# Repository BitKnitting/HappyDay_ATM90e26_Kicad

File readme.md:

## Version B

The B version of the HappyDay Energy PCB.  No changes to the schematic.  Several changes to the layout.  Corrected mistakes found while testing.

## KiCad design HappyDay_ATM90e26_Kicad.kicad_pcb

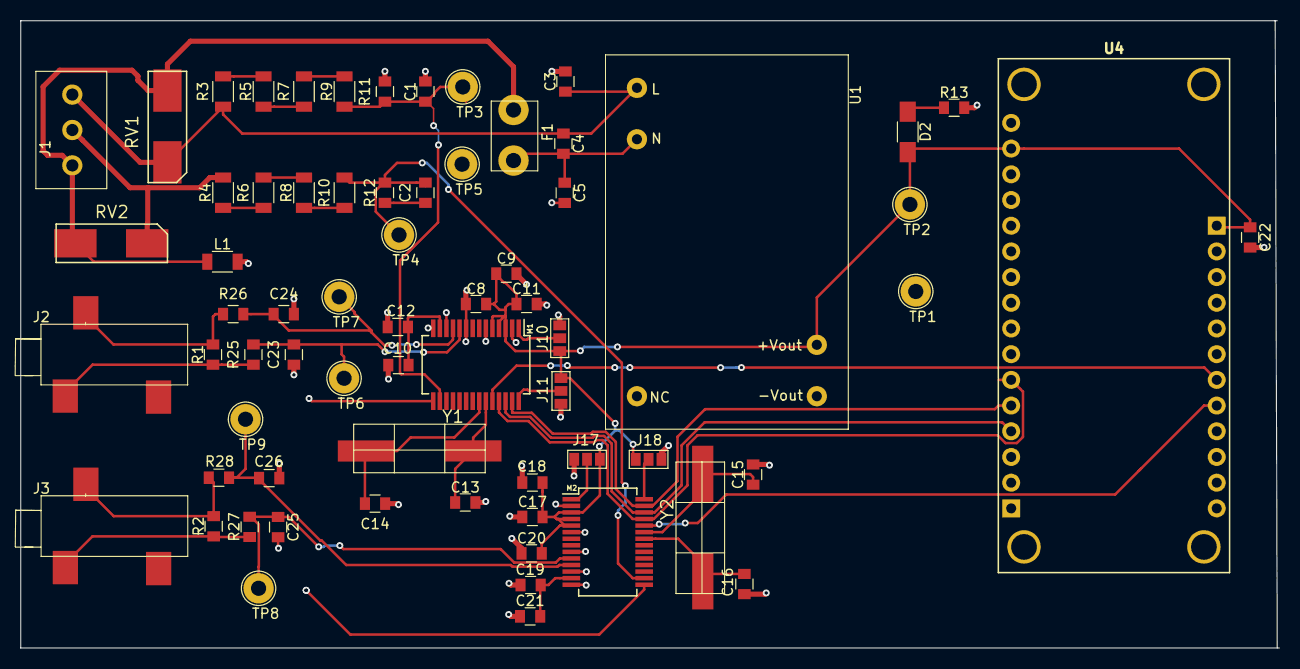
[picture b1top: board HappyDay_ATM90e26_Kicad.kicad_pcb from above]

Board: 2 copper layers, 124.4 x 62.0 mm, 68 parts (0 on the bottom side), 40 nets.

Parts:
C1, C2: .033u; C_0805
C3, C5: .001u; C_0805
C4, C8, C11, C12, C17, C20, C21, C22: .1u; C_0805
C9, C10, C18, C19: 10u; C_0805
C13, C14, C15, C16: 20p; C_0805
C23, C24, C25, C26: .33u; C_0805
D2: IND_LED; C_1206_HandSoldering
F1: Polyfuse; POLYFUSE
J1: Conn_01x03; 3PinConnector
J2, J3: TRS3.5; Audio-Jack
J10, J11, J17, J18: GS3
L1: Ferrite_Bead_Small; C_1206
M1, M2: ATM90E26_ATM90E26; SSOP-28_5.3x10.2mm_Pitch0.65mm
R1, R2: 12; C_0805
R3, R4, R5, R6, R7, R8, R9, R10: 220K; C_1206
R11, R12: 1K; C_0805
R13: 499; C_0805
R25, R26, R27, R28: 100; C_0805
RV1, RV2: Varistor; MOV
TP1: GNDD; Test_Point_Loop_D2.54mm_Drill1.5mm_Beaded
TP2: 3.3V; Test_Point_Loop_D2.54mm_Drill1.5mm_Beaded
TP3: LO_SAMP; Test_Point_Loop_D2.54mm_Drill1.5mm_Beaded
TP4: L1_SAMP; Test_Point_Loop_D2.54mm_Drill1.5mm_Beaded
TP5: GNDA; Test_Point_Loop_D2.54mm_Drill1.5mm_Beaded
TP6: IP_0; Test_Point_Loop_D2.54mm_Drill1.5mm_Beaded
TP7: IN_0; Test_Point_Loop_D2.54mm_Drill1.5mm_Beaded
TP8: IP_1; Test_Point_Loop_D2.54mm_Drill1.5mm_Beaded
TP9: IN_1; Test_Point_Loop_D2.54mm_Drill1.5mm_Beaded
U1: RAC03-3.3SGA; RAC03-GA
U4: FeatherHuzzah; ADAFRUIT_FEATHER
Y1, Y2: Crystal_Small; Crystal

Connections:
+3V3: C8.2, C9.1, C11.1, C17.2, C18.1, C20.1, C22.1, D2.2, J10.3, J11.1, J17.3, J18.1, M1.3, M1.4, M1.5, M2.3, M2.4, M2.5, TP2.1, U1.5, U4.15, U4.17
/ATM90_Circuit/CLKIN_0: C14.1, M1.22, Y1.2
/ATM90_Circuit/CLKIN_1: C16.1, M2.22, Y2.2
/ATM90_Circuit/CLKOUT_0: C13.1, M1.23, Y1.1
/ATM90_Circuit/CLKOUT_1: C15.1, M2.23, Y2.1
/ATM90_Circuit/CS0: M1.24, U4.23
/ATM90_Circuit/CS1: M2.24, U4.24
/ATM90_Circuit/MISO: M1.26, M2.26, U4.4
/ATM90_Circuit/MOSI: M1.27, M2.27, U4.5
/ATM90_Circuit/SCLK: M1.25, M2.25, U4.6
/IN_0: C24.2, M1.11, R26.1, TP7.1
/IN_1: C26.2, M2.11, R28.1, TP9.1
/IP_0: C23.1, M1.10, R25.1, TP6.1
/IP_1: C25.1, M2.10, R27.1, TP8.1
/L1: J1.2, R4.2, RV2.2
/L1_SAMP: C2.1, M2.16, R10.1, R12.2, TP4.1
/LO: C3.1, C4.1, J1.1, R3.2, RV1.2, U1.1
/LO_SAMP: C1.1, M1.16, R9.1, R11.2, TP3.1
/N: F1.2, J1.3, L1.1, RV1.1, RV2.1
GNDA: C1.2, C3.2, C5.2, C23.2, C24.1, C25.2, C26.1, L1.2, M1.15, M2.15, R11.1, TP5.1
GNDD: C8.1, C9.2, C10.2, C11.2, C12.2, C13.2, C14.2, C15.2, C16.2, C17.1, C18.2, C19.2, C20.2, C21.2, C22.2, J10.1, J11.3, J17.1, J18.3, M1.2, M1.6, M1.9, M1.12, M1.14, M2.2, M2.6, M2.9, M2.12, M2.14, R13.2, TP1.1, U1.4, U4.13
unnamed: C2.2, R12.1
unnamed: C4.2, C5.1, F1.1, U1.2
unnamed: C10.1, C12.1, M1.13
unnamed: C19.1, C21.1, M2.13
unnamed: D2.1, R13.1
unnamed: J2.1, R1.2, R26.2
unnamed: J2.2, R1.1, R25.2
unnamed: J3.1, R2.2, R28.2
unnamed: J3.2, R2.1, R27.2
unnamed: J10.2, M1.1
unnamed: J11.2, M1.28
unnamed: J17.2, M2.1
unnamed: J18.2, M2.28
unnamed: R3.1, R5.2
unnamed: R4.1, R6.2
unnamed: R5.1, R7.2
unnamed: R6.1, R8.2
unnamed: R7.1, R9.2
unnamed: R8.1, R10.2

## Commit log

2018-01-24 added rescue file
2018-01-24 added PDFs of Schematic
2018-01-28 added pdfs of PCB layout
2018-01-28 added readme.md to version_B
2018-02-17 added image of PCBs got back from OSHPark
2018-02-17 added kicad image of voltage sampling
2018-02-17 added voltage sampling test setup image
2018-02-17 added danger electricity image
2018-02-17 updated danger electricity image
2018-02-17 added current sampling kicad image
2018-02-18 added Arduino_AC_current_input_A.png image from OEM site
2018-02-18 added TRS_connector.png
2018-02-18 added scope_current_IP0_andIP1.png
2018-02-18 added test_lamp.jpg
2018-02-18 added RAC03-3.3SGA.png
2018-02-20 added cme0303s3c.png
2018-02-20 modified cme0303S3c.png
2018-02-20 added atm90e26_soldered_on_pcb.jpg
2018-02-20 added atm90e26_schematic.png;
2018-02-20 added Feather_on_PCB.jpg
2018-02-20 add Feather_pins_Schematic.png
2018-02-21 added Schematic_top_sheet.png
2018-02-21 added sense_power_cable.png
2018-02-21 added front_PCB_itemized.png
2018-02-21 added back_PCB_itemized.png
2018-02-21 added Schematic_meter_sheet.png
2018-02-21 added RAC03-caps-from-datasheet.png
2018-02-21 added atm90e26_short_circuit_solder.png
2018-02-21 added PCB_Layout_first_atm90e26_pins.png
2018-02-22 added Logic_analyzer_error.png
2018-02-24 Version b (#1)
    * added readme.md to version_B
    * added image of PCBs got back from OSHPark
    * added image of PCBs got back from OSHPark
    * added image of PCBs got back from OSHPark
    * added kicad image of voltage sampling
    * added voltage sampling test setup image
2018-02-24 added NorthAmerica_home_wiring.png and started updating schematic
2018-02-24 Version b (#2)
    * added readme.md to version_B
    * added image of PCBs got back from OSHPark
    * added image of PCBs got back from OSHPark
    * added image of PCBs got back from OSHPark
    * added kicad image of voltage sampling
    * added voltage sampling test setup image
2018-02-24 added 240VAC_in_from_transformer.png
2018-02-24 updated Voltage Sampling image part of Kicad schematic
2018-02-24 modified current_sampling_Kicad.png
2018-02-24 added Power_wires_coming_into_house.png
2018-02-24 added Voltage_sampling_voltage_divider.png
2018-02-24 ATM90E26_diagram_for_L0_Samp.png
2018-02-25 modified voltage_sample_voltage_divider.png
2018-02-25 modified ATM90E26_diagram_for_L0_Samp.png
2018-02-25 modified current_sampling_Kicad.png and schematic
2018-02-25 added current_sampling_pins_10_and_11_atm90e26_kicad.png
2018-02-27 updated design and layout sent to OSH Park (2/26/2018)
2018-03-02 added eeschema bom xml file
2018-03-02 added JBParts.csv
2018-03-04 added Feather_SPI.png and atm90e26_SPI.png
2018-03-06 changed oscillator caps to 27pf
2018-03-07 added SPI_pins_HUZZAH.png
2018-03-07 added Feather_Headers_on_schematic.png
2018-03-07 updated atm90e26_schematic.png
2018-03-07 added ATM90e26_Kicad.pdf
2018-03-07 added SPI_pins_RFM9X.png
2018-03-11 added datasheets
2018-03-15 added images/Feather_MISO_MOSI_SCKL.png
2018-03-16 added ATM90E26_SPI_FIGURE_3.png
2018-03-16 modified ATM90E26_SPI_FIGURE_3.png
2018-03-16 added SPI_CPOL_CPHA_FROM_HACKADAY_ARTICLE.png
